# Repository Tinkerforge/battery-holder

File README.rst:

Battery Holder
==============

**This Bricklet is currently in development.**

This repository contains the hardware design
files. The documentation generator configs can be found at
https://github.com/Tinkerforge/generators

Repository Content
------------------

hardware/:
 * Contains KiCad project files and additionally schematics as PDF

datasheets/:
 * Contains datasheets for sensors and complex ICs that are used

Hardware
--------

The hardware is designed with the open source EDA Suite KiCad
(http://www.kicad.org). Before you are able to open the files,
you have to install the Tinkerforge kicad-libraries
(https://github.com/Tinkerforge/kicad-libraries). You can either clone
them directly in hardware/ or clone them in a separate folder and
symlink them into hardware/
(ln -s kicad_path/kicad-libraries project_path/hardware). After that you
can open the .pro file in hardware/ with KiCad and from there view and
modify the schematics and the PCB layout.

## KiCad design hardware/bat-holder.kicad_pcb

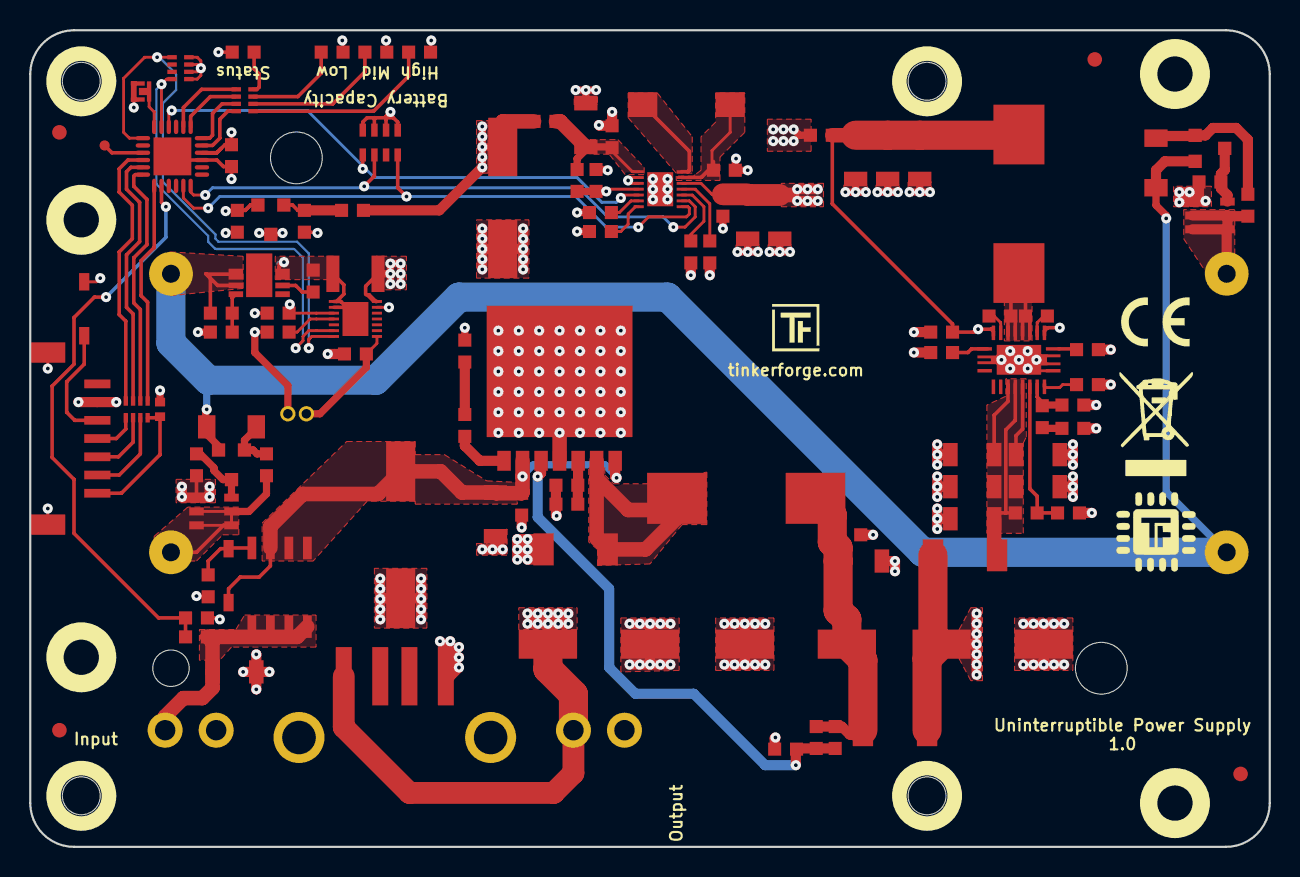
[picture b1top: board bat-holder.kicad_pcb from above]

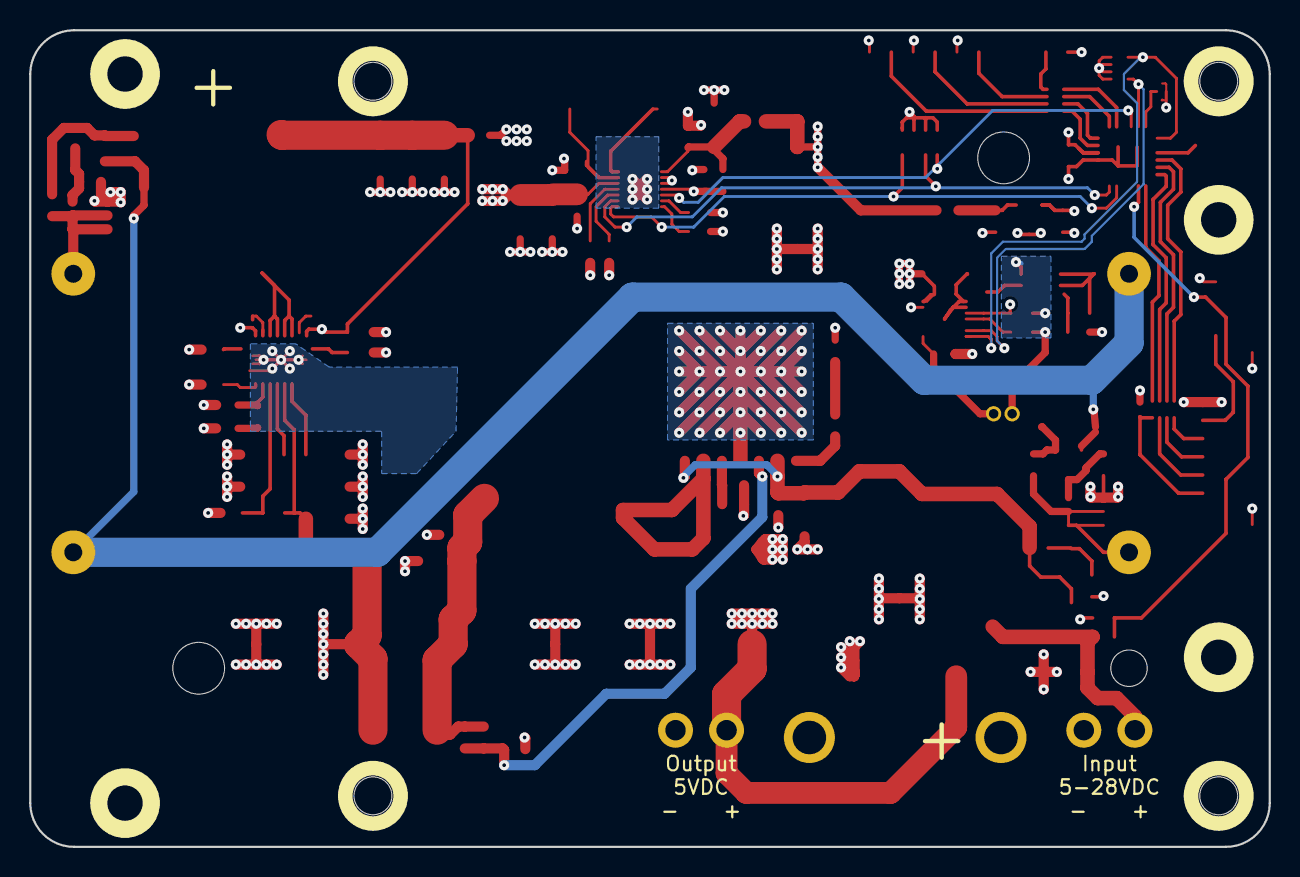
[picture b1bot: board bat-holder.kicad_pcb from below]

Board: 4 copper layers, 85.0 x 56.0 mm, 121 parts (2 on the bottom side), 70 nets.

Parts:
C101, C102, C209, C220, C228, C230: 100nF; C0603F
C103: 220pF; C0402F
C104, C204, C207, C222, C224: 100nF/16V; C0603F
C105: 470nF; C0603F
C106, C225, C229, C233: 470µF/16V; ELKO_83
C107, C108, C226: 1uF; C0603F
C201, C202, C203, C208, C214, C215, C216, C217, C218, C221, C223, C231, C232: 10uF; C1206
C205: 2.2uF; C0603F
C206: UWT1H221MNL1GS; ELKO_103
C210: 8.2nF; C0603F
C211: 100pF; C0603F
C212: 36pF; C0603F
C213: 680pF; C0603F
C219: 4.7nF; C0603F
C227: DNP; C0603F
D101, D102: LL4148; MiniMelf
D103: blue; D0603F
D104, D105, D106: green; D0603F
D107: B0520LW-7; SOD-123
D201: Z12V; SOD-123
D202, D203, D204: PMEG6045; SOD-128
Fiducial_Mark: VAL**; Fiducial_Mark
Fiducial_Mark#2, Fiducial_Mark#3, Fiducial_Mark#4: VAL**; Fiducial_Mark
J101: BAT_1049P
J102: USB-A; USB-A-SMT-8231
K101: NTC; Pin_Header_Straight_1x02_127
L201: 1uH 74437368010; WE-LHMI
L202: 22uH 74437368220; WE-LHMI
L203: 4.7uH 7447789004; WE-PD
P101: BOOT; SolderJumper
P102: DEBUG; DEBUG_PAD
P103: CON-SENSOR2
P105: 5V Out; OQ_2P
P201: Input; OQ_2P
Q101, Q102: BC846; SOT23EBC
Q103, Q104: DMP2035UVTQ; SOT26GDS
Q201: Si4447ADY; SOIC-8-MOSFET
R1, R2, R3: 0; R0603F
R101, R102, R103, R104, R202, R204, R221: 10k; R0603F
R107: 330; R0603F
R108: 2.7k; R0603F
R109: DNP; R0603F
R110: 10m; R1210
R201: VC120626D580DP; R1206
R203: 1k; R0603F
R205: 332k; R0603F
R206: 105k TBD; R0603F
R207: 27; R0603F
R208: 36.5k; R0603F
R209: 309k; R0603F
R210: 86.6k; R0603F
R211: 20k; R0603F
R212: 100; R0603F
R213: 47k; R0603F
R214: 8.2k; R0603F
R217: 49.9k; R0603F
R219: 100k; R0603F
RP101: 1k; 4X0402
RP102: 82; 4X0402
RP103: 10k; 4X0402
RP201: 1k; 4X0603
U101: XMC1XXX24; QFN24-4x4mm-0.5mm
U102: AP9211; DFN2030-6
U103: MAX17260_LS; TDFN14-3x3
U104, U105, U106, U107: DRILL; DRILL_NP
U108, U109, U110, U111: DRILL; DRILL_26
U112: AP7333-33SA; SOT23-3
U201: TPS61088RHL; VQFN20_45x35
U202: BD906XX-C-HRP7
U203: AAT3620; TDFN14-3x3
VAL: CE_5mm
VAL#2: WEEE_7mm

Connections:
3V3: C101.1, C108.2, D103.1, D104.1, D105.1, D106.1, D107.2, RP103.5, RP103.6, RP103.7, RP103.8, RP201.1, RP201.2, RP201.3, RP201.4, U101.10, U112.2
5VOUT: C214.1, C215.1, C216.1, C217.1, C218.1, D202.1, R209.1, U201.14, U201.15, U201.16
+5V: C106.1, C229.1, C233.1, D202.2, D204.2, J102.1, P105.1, R1.2, R3.2
AGND: C104.2, C105.1, K101.2, R108.1, R110.1, U102.6, U103.8, U103.9, U103.EP
BATTERY-SCL: RP103.1, U101.19, U103.14
BATTERY-SDA: RP103.4, U101.17, U103.13
BAT_OUT: C104.1, C230.1, C231.1, C232.1, Q103.S, Q104.S, R2.1, R103.2, R104.2, R107.2, R109.2, U103.6, U103.10, U203.12
CHARGER_EN: RP201.8, U101.16, U203.5
CHARGER_STAT1: RP201.7, U101.6, U203.9
CHARGER_STAT2: RP201.5, U101.5, U203.8
CHG_IN: C207.2, L201.2, R205.2, U201.4, U201.5, U201.6, U201.7
DC-IN-VOLTAGE: R202.2, R203.1, U101.2
GBAT: C102.2, D101.1, D102.1, J101.2, J101.4, Q101.E, Q102.E, U102.1, U102.2
GND: C101.2, C103.2, C106.2, C107.1, C108.1, C201.2, C202.2, C203.2, C204.2, C205.2, C206.2, C208.2, C209.2, C210.2, C211.2, C212.2, C213.2, C214.2, C215.2, C216.2, C217.2, C218.2, C219.2, C220.2, C221.2, C222.2, C223.2, C224.2, C225.2, C226.2, C228.2, C229.2, C230.2, C231.2, C232.2, C233.2, D203.1, J102.4, J102.SHD, P101.1, P103.2, P103.EP, P105.2, P201.2, R110.2, R201.2, R203.2, R204.2, R206.2, R207.1, R210.2, R214.1, R217.2, R219.2, U101.9, U101.EXP, U103.7, U112.3, U201.20, U201.EXP, U202.4, U202.EXP, U203.2, U203.3, U203.EP
L1: L203.2, U203.14
L2: C228.1, L203.1, U203.13
unnamed: C102.1, R107.1, U102.3
unnamed: C103.1, P103.7, RP102.4
unnamed: C105.2, U103.11
unnamed: C107.2, R1.1, U112.1
unnamed: C201.1, C202.1, C203.1, C204.1, L201.1, R2.2, U201.2, U201.9
unnamed: C205.1, U201.1
unnamed: C207.1, U201.8
unnamed: C210.1, U201.10
unnamed: C211.1, R207.2, U202.5
unnamed: C212.1, R208.1, U201.18
unnamed: C213.1, R208.2
unnamed: C219.1, R211.1
unnamed: C220.1, C223.1, C225.1, C227.1, D204.1, L202.2, R213.2
unnamed: C221.1, C222.1, R3.1, R212.1, U203.1
unnamed: C224.1, U203.7
unnamed: C227.2, R213.1, R214.2, U202.3
unnamed: D101.2, Q101.B, R101.1
unnamed: D102.2, Q102.B, R102.1
unnamed: D103.2, RP101.8
unnamed: D104.2, RP101.7
unnamed: D105.2, RP101.6
unnamed: D106.2, RP101.5
unnamed: D107.1, P103.3
unnamed: D201.1, Q201.G, R204.1
unnamed: K101.1, R109.1, U103.1
unnamed: P101.2, U101.18
unnamed: P102.1, U101.21
unnamed: P103.4, RP102.1
unnamed: P103.5, RP102.2
unnamed: P103.6, RP102.3
unnamed: Q101.C, Q103.G, R103.1
unnamed: Q102.C, Q104.G, R104.1
unnamed: R108.2, U102.5
unnamed: R205.1, U201.3
unnamed: R206.1, U201.19
unnamed: R209.2, R210.1, U201.17
unnamed: R211.2, U202.1
unnamed: R217.1, U203.10
unnamed: R219.1, U203.6
unnamed: R221.2, U203.11
unnamed: RP101.1, U101.14
unnamed: RP101.2, U101.13
unnamed: RP101.3, U101.12
unnamed: RP101.4, U101.11
SPI-CLK: RP102.7, U101.23
SPI-CS: RP102.8, U101.22
SPI-MISO: RP102.5, U101.1
SPI-MOSI: RP102.6, U101.24
VBAT1: J101.1, Q103.D, R101.2
VBAT2: J101.3, Q104.D, R102.2
VCC: C226.1, R212.2, R221.1, U203.4
VIN: P201.1, Q201.D, R201.1, R202.1
VIN2: C206.1, C208.1, C209.1, D201.2, Q201.S, U202.2, U202.7
VSW: D203.2, L202.1, U202.6

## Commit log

2018-10-24 prototype hardware checkin
2018-11-14 change to ap9211 battery protection ic
2018-11-14 add battery hint
2018-11-20 add hint, add datasheet
2018-11-23 change reverse polarity protection of batteries
2018-11-23 change ntc routing
2018-11-23 add debugging resistors
2018-12-06 fix bc846 footprints, fix connector orientation
2019-03-01 routing nearly completed
2019-03-04 fully routed
2019-03-04 prototype finished
2019-03-04 change settings
2019-03-04 add sym lib table
2019-03-25 fix diode footprint
2019-03-29 changed slikscreentext on bottomlayer <Output 5VDC>
2019-04-08 added 0 ohm resistors and extented footprints for prototyping
2021-10-25 Update KiCad link
    https://www.kicad.org/blog/2021/10/Avoid-links-to-former-kicad-domain/

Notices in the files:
hardware/bat-holder.kicad_pcb:
Licensed under CERN OHL v.1.1
Copyright (©) 2018, B.Nordmeyer
Copyright Tinkerforge GmbH 2018.
This documentation describes Open Hardware and is licensed under the
CERN OHL v. 1.1.
